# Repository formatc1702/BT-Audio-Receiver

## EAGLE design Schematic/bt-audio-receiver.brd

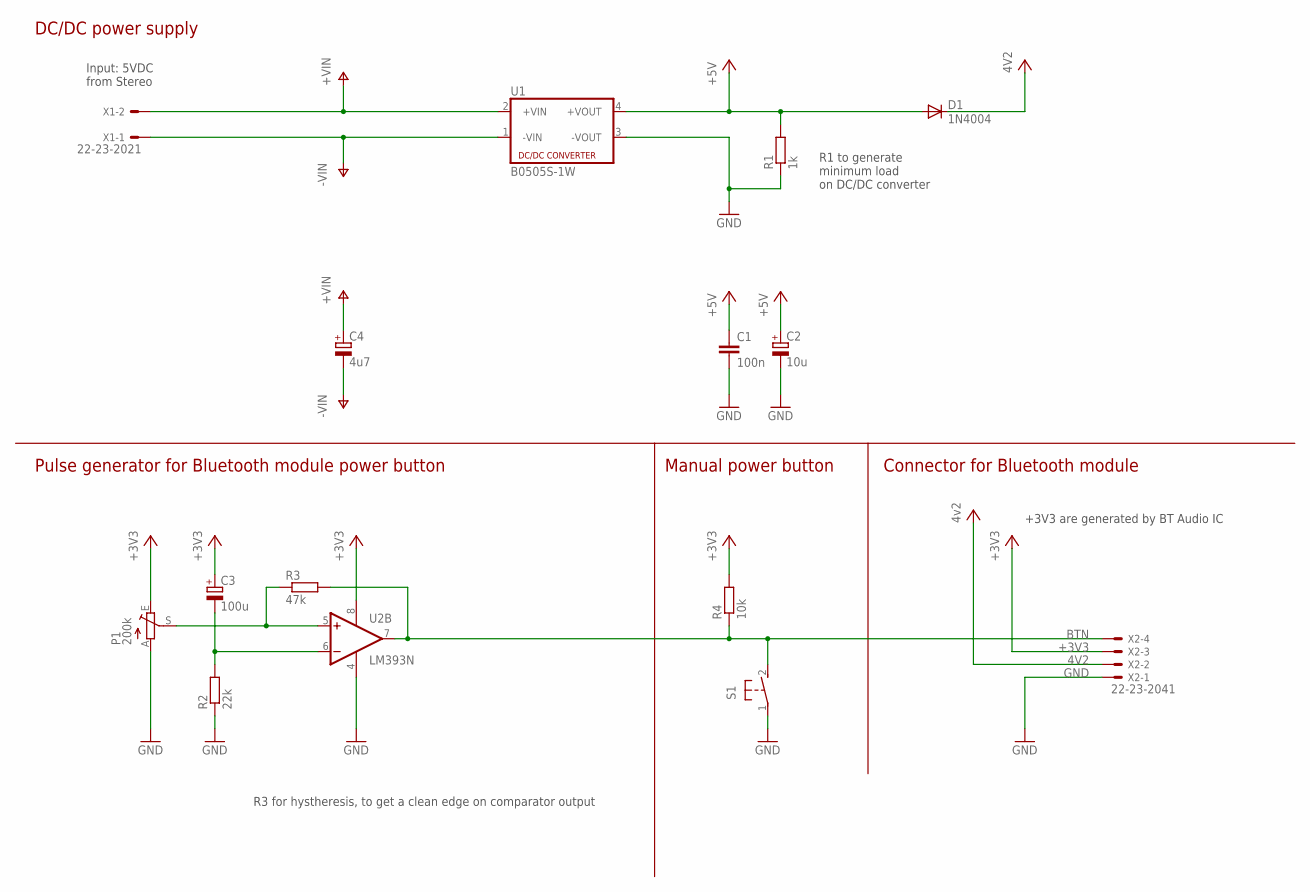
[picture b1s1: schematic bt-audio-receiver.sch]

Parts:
C1: 100n; C025-025X050
C2: 10u; E2-4
C3: 100u; E2,5-5
C4: 4u7; E2-4
D1: 1N4004; DO41-10
P1: 200k; B25P
R1: 1k; 0204V
R2: 22k; 0204/7
R3: 47k; 0204/5
R4: 10k; 0204V
S1: DTS-3
U1: B0505S-1W; 4SIL
U2: LM393N; DIL08
X1: 22-23-2021
X2: 22-23-2041

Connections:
4V2: D1.C, X2.2
+3V3: C3.+, P1.E, R4.2, U2.8 (V+), X2.3
+5V: C1.1, C2.+, D1.A, R1.2, U1.4 (+VOUT)
+VIN: C4.+, U1.2 (+VIN), X1.2
-VIN: C4.-, U1.1 (-VIN), X1.1
BTN: R3.2, R4.1, S1.2, U2.7 (OUT), X2.4
GND: C1.2, C2.-, P1.A, R1.1, R2.1, S1.1, U1.3 (-VOUT), U2.4 (V-), X2.1
unnamed: C3.-, R2.2, U2.6 (-IN)
unnamed: P1.S, R3.1, U2.5 (+IN)

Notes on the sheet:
+3V3 are generated by BT Audio IC
R3 for hystheresis, to get a clean edge on comparator output
DC/DC power supply
Pulse generator for Bluetooth module power button
Manual power button
Connector for Bluetooth module
Input: 5VDC from Stereo
R1 to generate minimum load on DC/DC converter

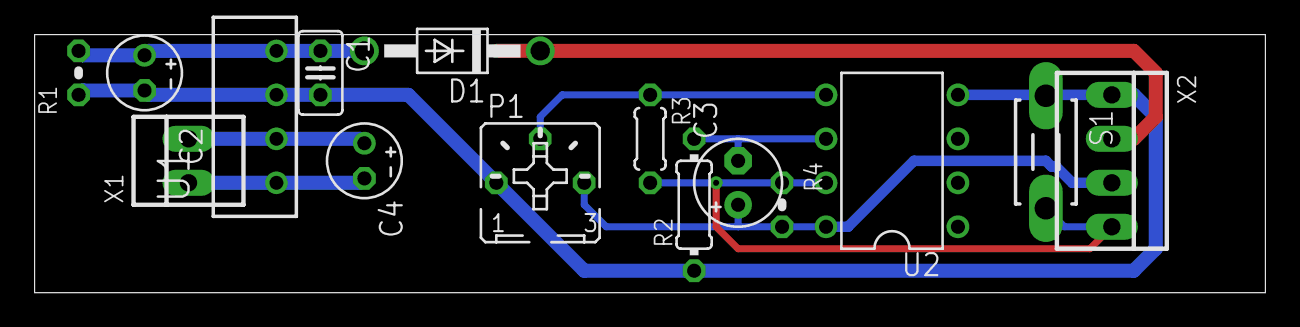
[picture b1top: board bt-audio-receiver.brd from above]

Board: 2 copper layers, 71.1 x 14.9 mm, 15 parts (0 on the bottom side), 9 nets.

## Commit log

2020-05-11 Add photos
2020-05-11 Add schematic PDF
2020-05-11 Update schematic
